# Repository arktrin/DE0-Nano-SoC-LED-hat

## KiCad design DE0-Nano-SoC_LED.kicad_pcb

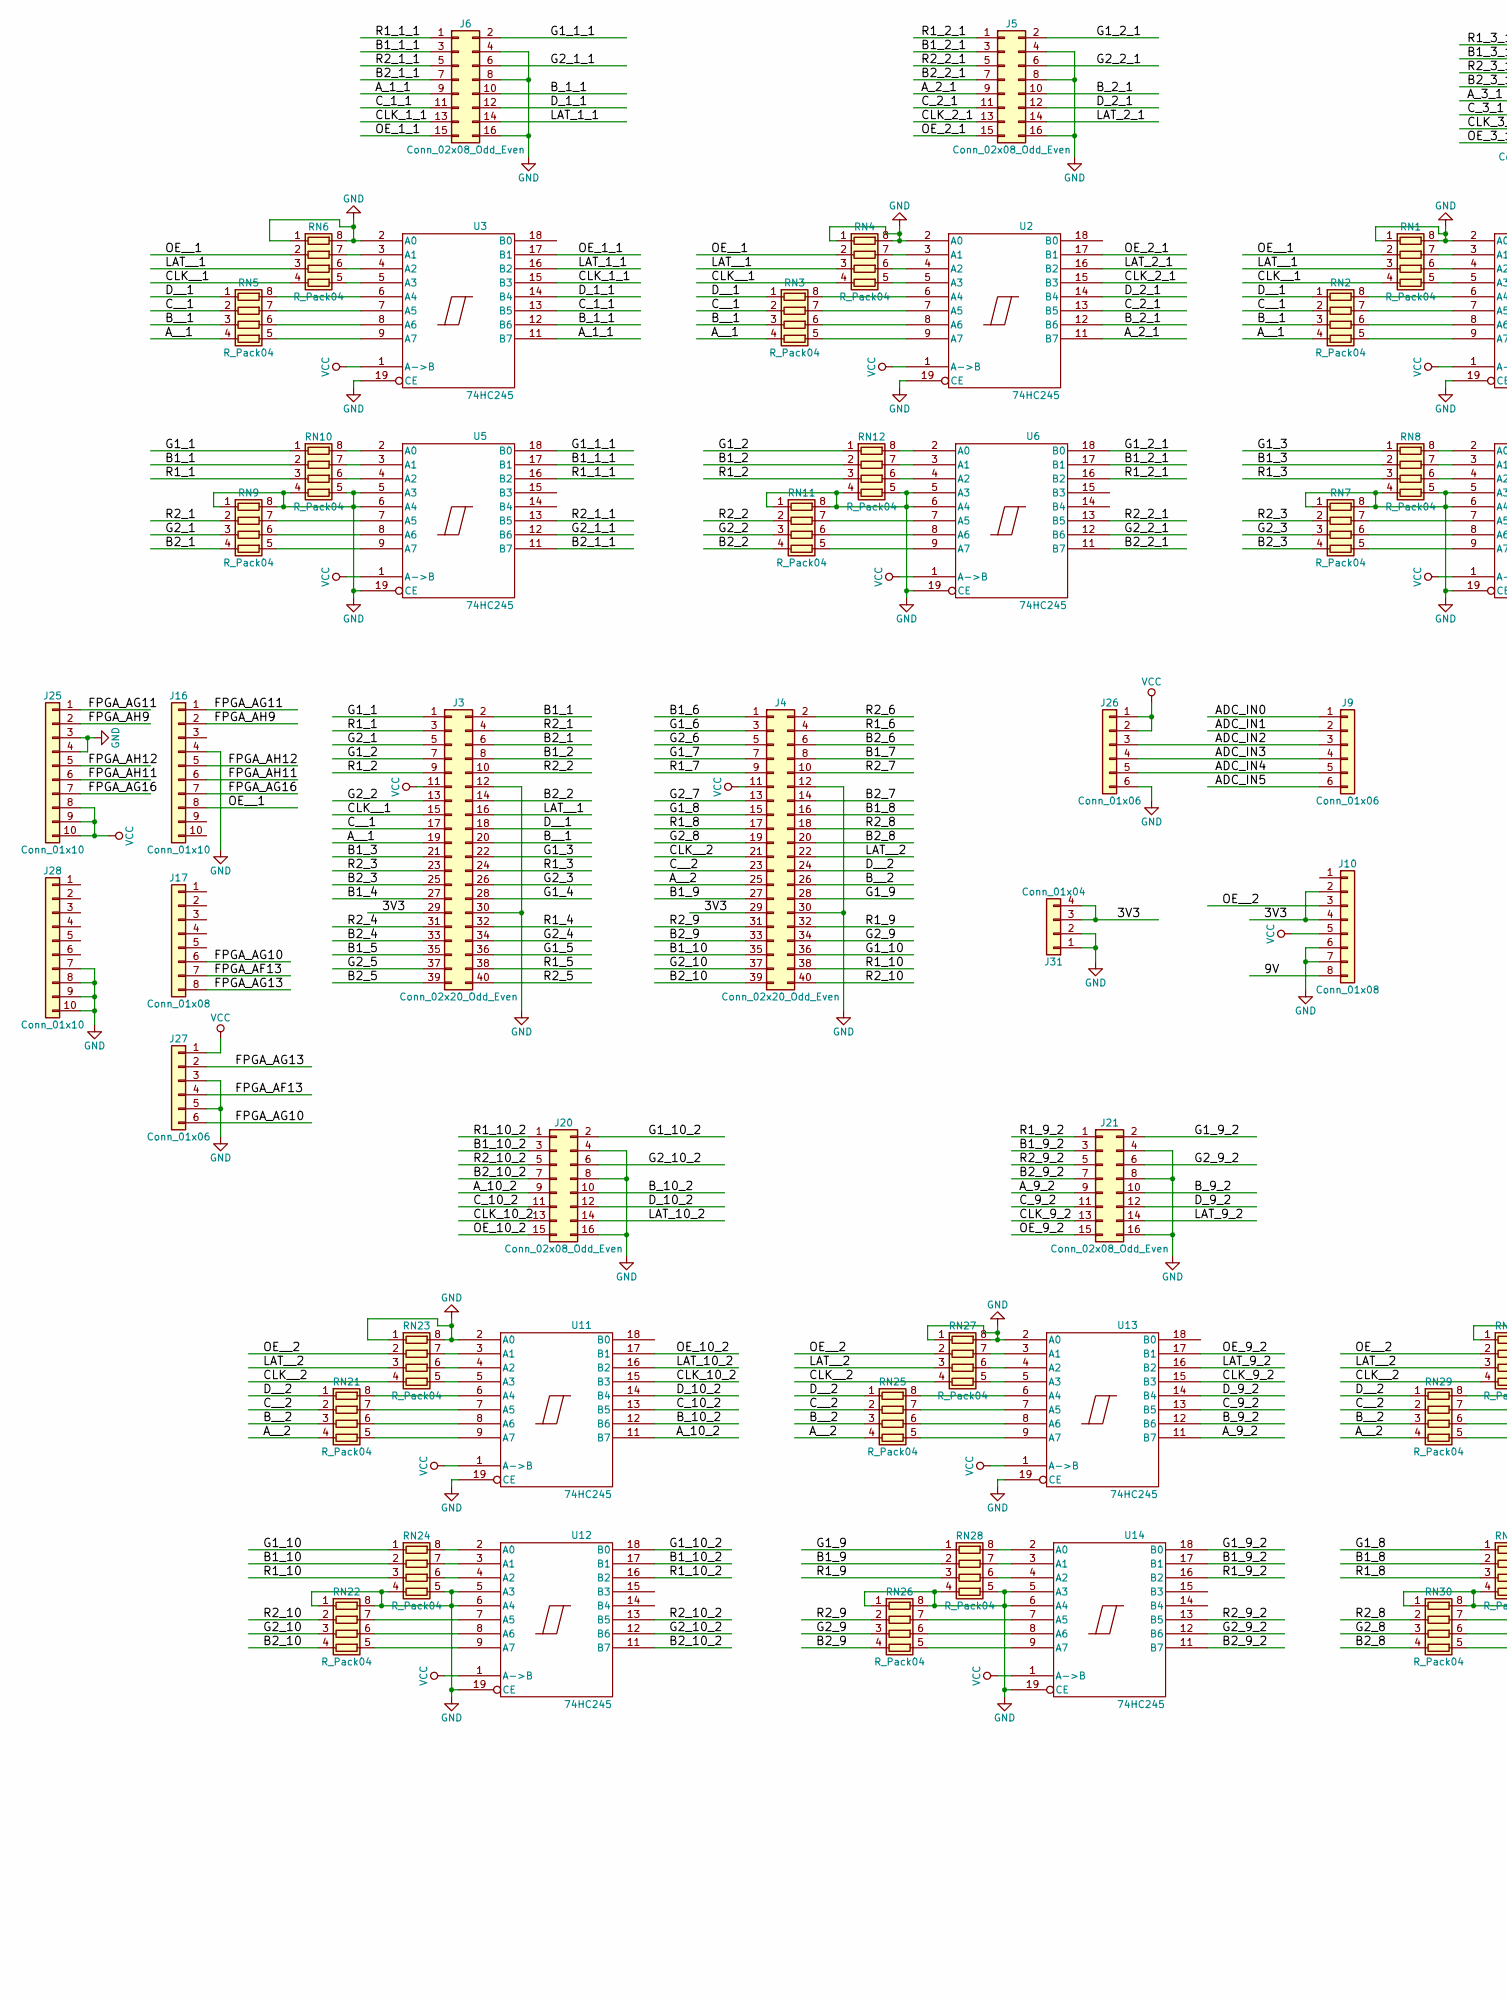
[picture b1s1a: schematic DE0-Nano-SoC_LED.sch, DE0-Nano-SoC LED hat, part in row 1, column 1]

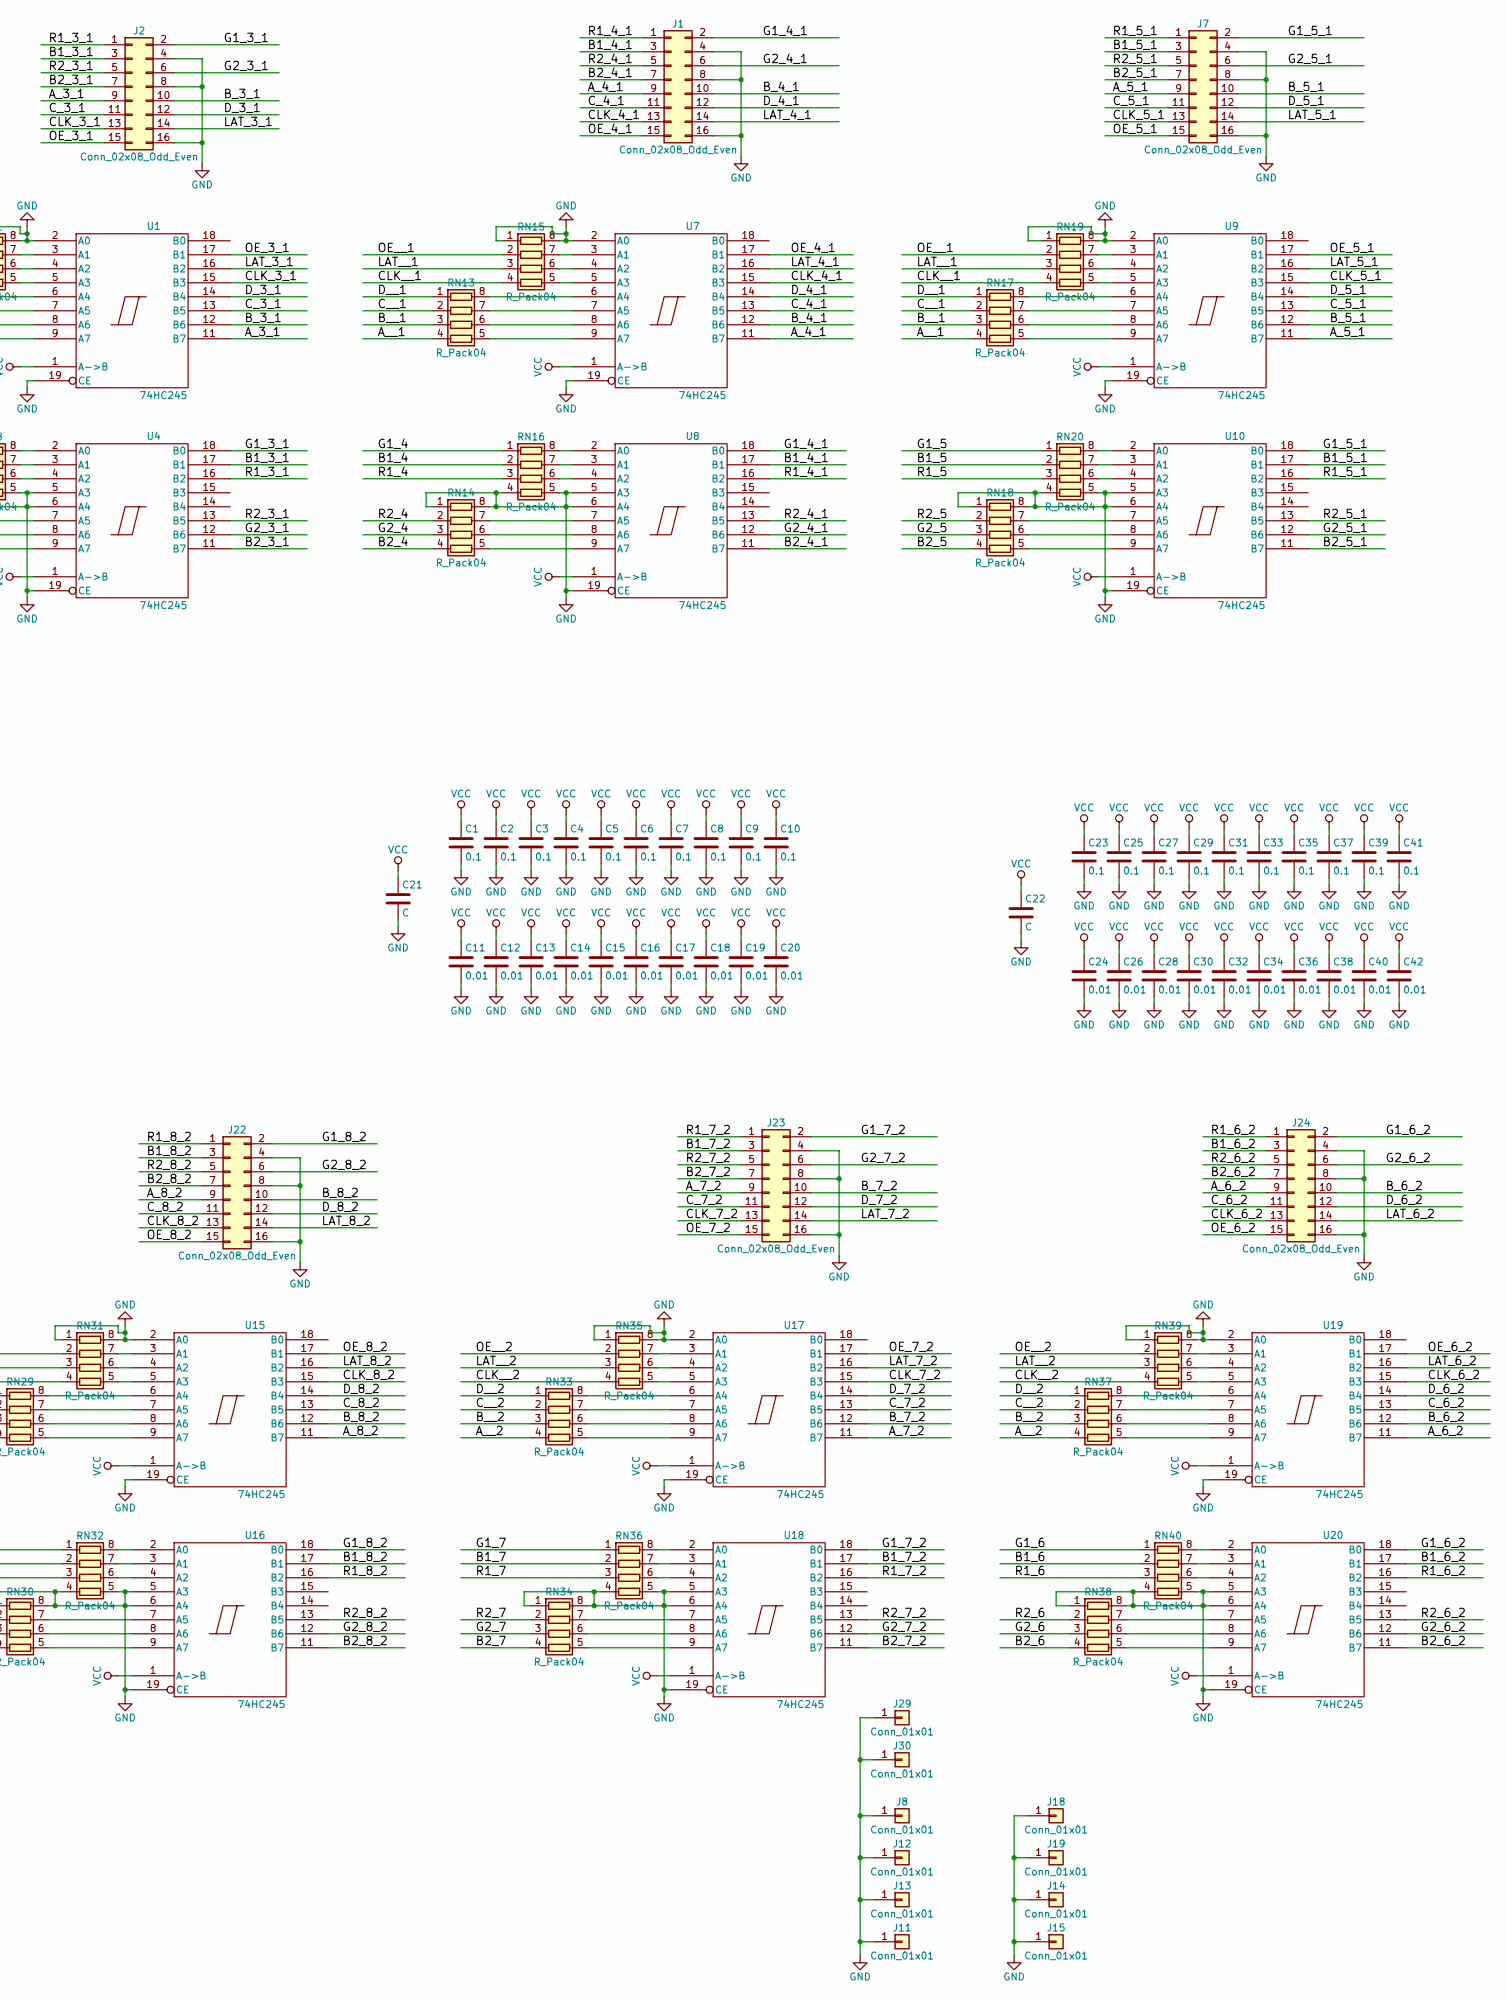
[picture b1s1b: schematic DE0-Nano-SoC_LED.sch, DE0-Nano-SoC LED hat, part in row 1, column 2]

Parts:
C1, C2, C3, C4, C5, C6, C7, C8, C9, C10, C23, C25, C27, C29, C31, C33, C35, C37, C39, C41: 0.1; C_0402_NoSilk
C11, C12, C13, C14, C15, C16, C17, C18, C19, C20, C24, C26, C28, C30, C32, C34, C36, C38, C40, C42: 0.01; C_0402_NoSilk
C21, C22: C; C_1210
J1, J2, J5, J6, J7, J20, J21, J22, J23, J24: Conn_02x08_Odd_Even; Multicomp_MC9A12-1634_2x08x2.54mm_Straight
J3, J4: Conn_02x20_Odd_Even; Pin_Header_Straight_2x20_Pitch2.54mm
J8, J11, J12, J13, J14, J15, J18, J19, J29, J30: Conn_01x01; MountingHole_3.2mm_M3_ISO7380_Pad
J9, J26, J27: Conn_01x06; Pin_Header_Straight_1x06_Pitch2.54mm
J10, J17: Conn_01x08; Pin_Header_Straight_1x08_Pitch2.54mm
J16, J25, J28: Conn_01x10; Pin_Header_Straight_1x10_Pitch2.54mm
J31: Conn_01x04; Pin_Header_Straight_1x04_Pitch2.54mm
RN1, RN2, RN3, RN4, RN5, RN6, RN7, RN8, RN9, RN10, RN11, RN12, RN13, RN14, RN15, RN16, RN17, RN18, RN19, RN20, RN21, RN22, RN23, RN24, RN25, RN26, RN27, RN28, RN29, RN30, RN31, RN32, RN33, RN34, RN35, RN36, RN37, RN38, RN39, RN40: R_Pack04; R_Array_Concave_4x0402
U1, U2, U3, U4, U5, U6, U7, U8, U9, U10, U11, U12, U13, U14, U15, U16, U17, U18, U19, U20: 74HC245; SSOP-20

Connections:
/3V3: J3.29, J4.29, J10.2, J10.4, J31.3, J31.4
/ADC_IN2: J9.3, J26.3
/ADC_IN3: J9.4, J26.4
/ADC_IN4: J9.5, J26.5
/ADC_IN5: J9.6
/A_1_1: J6.9, U3.11 (B7)
/A_2_1: J5.9, U2.11 (B7)
/A_3_1: J2.9, U1.11 (B7)
/A_4_1: J1.9, U7.11 (B7)
/A_5_1: J7.9, U9.11 (B7)
/A_6_2: J24.9, U19.11 (B7)
/A_7_2: J23.9, U17.11 (B7)
/A_8_2: J22.9, U15.11 (B7)
/A_9_2: J21.9, U13.11 (B7)
/A_10_2: J20.9, U11.11 (B7)
/A__1: J3.19, RN2.4 (R4.1), RN3.4 (R4.1), RN5.4 (R4.1), RN13.4 (R4.1), RN17.4 (R4.1)
/A__2: J4.25, RN21.4 (R4.1), RN25.4 (R4.1), RN29.4 (R4.1), RN33.4 (R4.1), RN37.4 (R4.1)
/B1_1: J3.2, RN10.2 (R2.1)
/B1_1_1: J6.3, U5.17 (B1)
/B1_2: J3.8, RN12.2 (R2.1)
/B1_2_1: J5.3, U6.17 (B1)
/B1_3: J3.21, RN8.2 (R2.1)
/B1_3_1: J2.3, U4.17 (B1)
/B1_4: J3.27, RN16.2 (R2.1)
/B1_4_1: J1.3, U8.17 (B1)
/B1_5: J3.35, RN20.2 (R2.1)
/B1_5_1: J7.3, U10.17 (B1)
/B1_6: J4.1, RN40.2 (R2.1)
/B1_6_2: J24.3, U20.17 (B1)
/B1_7: J4.8, RN36.2 (R2.1)
/B1_7_2: J23.3, U18.17 (B1)
/B1_8: J4.16, RN32.2 (R2.1)
/B1_8_2: J22.3, U16.17 (B1)
/B1_9: J4.27, RN28.2 (R2.1)
/B1_9_2: J21.3, U14.17 (B1)
/B1_10: J4.35, RN24.2 (R2.1)
/B1_10_2: J20.3, U12.17 (B1)
/B2_1: J3.6, RN9.4 (R4.1)
/B2_1_1: J6.7, U5.11 (B7)
/B2_2: J3.14, RN11.4 (R4.1)
/B2_2_1: J5.7, U6.11 (B7)
/B2_3: J3.25, RN7.4 (R4.1)
/B2_3_1: J2.7, U4.11 (B7)
/B2_4: J3.33, RN14.4 (R4.1)
/B2_4_1: J1.7, U8.11 (B7)
/B2_5: J3.39, RN18.4 (R4.1)
/B2_5_1: J7.7, U10.11 (B7)
/B2_6: J4.6, RN38.4 (R4.1)
/B2_6_2: J24.7, U20.11 (B7)
/B2_7: J4.14, RN34.4 (R4.1)
/B2_7_2: J23.7, U18.11 (B7)
/B2_8: J4.20, RN30.4 (R4.1)
/B2_8_2: J22.7, U16.11 (B7)
/B2_9: J4.33, RN26.4 (R4.1)
/B2_9_2: J21.7, U14.11 (B7)
/B2_10: J4.39, RN22.4 (R4.1)
/B2_10_2: J20.7, U12.11 (B7)
/B_1_1: J6.10, U3.12 (B6)
/B_2_1: J5.10, U2.12 (B6)
/B_3_1: J2.10, U1.12 (B6)
/B_4_1: J1.10, U7.12 (B6)
/B_5_1: J7.10, U9.12 (B6)
/B_6_2: J24.10, U19.12 (B6)
/B_7_2: J23.10, U17.12 (B6)
/B_8_2: J22.10, U15.12 (B6)
/B_9_2: J21.10, U13.12 (B6)
/B_10_2: J20.10, U11.12 (B6)
/B__1: J3.20, RN2.3 (R3.1), RN3.3 (R3.1), RN5.3 (R3.1), RN13.3 (R3.1), RN17.3 (R3.1)
/B__2: J4.26, RN21.3 (R3.1), RN25.3 (R3.1), RN29.3 (R3.1), RN33.3 (R3.1), RN37.3 (R3.1)
/CLK_1_1: J6.13, U3.15 (B3)
/CLK_2_1: J5.13, U2.15 (B3)
/CLK_3_1: J2.13, U1.15 (B3)
/CLK_4_1: J1.13, U7.15 (B3)
/CLK_5_1: J7.13, U9.15 (B3)
/CLK_6_2: J24.13, U19.15 (B3)
/CLK_7_2: J23.13, U17.15 (B3)
/CLK_8_2: J22.13, U15.15 (B3)
/CLK_9_2: J21.13, U13.15 (B3)
/CLK_10_2: J20.13, U11.15 (B3)
/CLK__1: J3.15, RN1.4 (R4.1), RN4.4 (R4.1), RN6.4 (R4.1), RN15.4 (R4.1), RN19.4 (R4.1)
/CLK__2: J4.21, RN23.4 (R4.1), RN27.4 (R4.1), RN31.4 (R4.1), RN35.4 (R4.1), RN39.4 (R4.1)
/C_1_1: J6.11, U3.13 (B5)
/C_2_1: J5.11, U2.13 (B5)
/C_3_1: J2.11, U1.13 (B5)
/C_4_1: J1.11, U7.13 (B5)
/C_5_1: J7.11, U9.13 (B5)
/C_6_2: J24.11, U19.13 (B5)
/C_7_2: J23.11, U17.13 (B5)
/C_8_2: J22.11, U15.13 (B5)
/C_9_2: J21.11, U13.13 (B5)
/C_10_2: J20.11, U11.13 (B5)
/C__1: J3.17, RN2.2 (R2.1), RN3.2 (R2.1), RN5.2 (R2.1), RN13.2 (R2.1), RN17.2 (R2.1)
/C__2: J4.23, RN21.2 (R2.1), RN25.2 (R2.1), RN29.2 (R2.1), RN33.2 (R2.1), RN37.2 (R2.1)
/D_1_1: J6.12, U3.14 (B4)
/D_2_1: J5.12, U2.14 (B4)
/D_3_1: J2.12, U1.14 (B4)
/D_4_1: J1.12, U7.14 (B4)
/D_5_1: J7.12, U9.14 (B4)
/D_6_2: J24.12, U19.14 (B4)
/D_7_2: J23.12, U17.14 (B4)
/D_8_2: J22.12, U15.14 (B4)
/D_9_2: J21.12, U13.14 (B4)
/D_10_2: J20.12, U11.14 (B4)
/D__1: J3.18, RN2.1 (R1.1), RN3.1 (R1.1), RN5.1 (R1.1), RN13.1 (R1.1), RN17.1 (R1.1)
/D__2: J4.24, RN21.1 (R1.1), RN25.1 (R1.1), RN29.1 (R1.1), RN33.1 (R1.1), RN37.1 (R1.1)
/FPGA_AF13: J17.7, J27.4
/FPGA_AG10: J17.6, J27.6
/FPGA_AG11: J16.1, J25.1
/FPGA_AG13: J17.8, J27.2
/FPGA_AG16: J16.7, J25.7
/FPGA_AH9: J16.2, J25.2
/FPGA_AH11: J16.6, J25.6
/FPGA_AH12: J16.5, J25.5
/G1_1: J3.1, RN10.1 (R1.1)
/G1_1_1: J6.2, U5.18 (B0)
/G1_2: J3.7, RN12.1 (R1.1)
/G1_2_1: J5.2, U6.18 (B0)
/G1_3: J3.22, RN8.1 (R1.1)
/G1_3_1: J2.2, U4.18 (B0)
/G1_4: J3.28, RN16.1 (R1.1)
/G1_4_1: J1.2, U8.18 (B0)
/G1_5: J3.36, RN20.1 (R1.1)
/G1_5_1: J7.2, U10.18 (B0)
/G1_6: J4.3, RN40.1 (R1.1)
/G1_6_2: J24.2, U20.18 (B0)
/G1_7: J4.7, RN36.1 (R1.1)
/G1_7_2: J23.2, U18.18 (B0)
/G1_8: J4.15, RN32.1 (R1.1)
/G1_8_2: J22.2, U16.18 (B0)
/G1_9: J4.28, RN28.1 (R1.1)
/G1_9_2: J21.2, U14.18 (B0)
/G1_10: J4.36, RN24.1 (R1.1)
/G1_10_2: J20.2, U12.18 (B0)
/G2_1: J3.5, RN9.3 (R3.1)
/G2_1_1: J6.6, U5.12 (B6)
/G2_2: J3.13, RN11.3 (R3.1)
/G2_2_1: J5.6, U6.12 (B6)
/G2_3: J3.26, RN7.3 (R3.1)
/G2_3_1: J2.6, U4.12 (B6)
/G2_4: J3.34, RN14.3 (R3.1)
/G2_4_1: J1.6, U8.12 (B6)
/G2_5: J3.37, RN18.3 (R3.1)
/G2_5_1: J7.6, U10.12 (B6)
/G2_6: J4.5, RN38.3 (R3.1)
/G2_6_2: J24.6, U20.12 (B6)
/G2_7: J4.13, RN34.3 (R3.1)
/G2_7_2: J23.6, U18.12 (B6)
/G2_8: J4.19, RN30.3 (R3.1)
/G2_8_2: J22.6, U16.12 (B6)
/G2_9: J4.34, RN26.3 (R3.1)
/G2_9_2: J21.6, U14.12 (B6)
/G2_10: J4.37, RN22.3 (R3.1)
/G2_10_2: J20.6, U12.12 (B6)
/LAT_1_1: J6.14, U3.16 (B2)
/LAT_2_1: J5.14, U2.16 (B2)
/LAT_3_1: J2.14, U1.16 (B2)
/LAT_4_1: J1.14, U7.16 (B2)
/LAT_5_1: J7.14, U9.16 (B2)
/LAT_6_2: J24.14, U19.16 (B2)
/LAT_7_2: J23.14, U17.16 (B2)
/LAT_8_2: J22.14, U15.16 (B2)
/LAT_9_2: J21.14, U13.16 (B2)
/LAT_10_2: J20.14, U11.16 (B2)
/LAT__1: J3.16, RN1.3 (R3.1), RN4.3 (R3.1), RN6.3 (R3.1), RN15.3 (R3.1), RN19.3 (R3.1)
/LAT__2: J4.22, RN23.3 (R3.1), RN27.3 (R3.1), RN31.3 (R3.1), RN35.3 (R3.1), RN39.3 (R3.1)
/OE_1_1: J6.15, U3.17 (B1)
/OE_2_1: J5.15, U2.17 (B1)
/OE_3_1: J2.15, U1.17 (B1)
/OE_4_1: J1.15, U7.17 (B1)
/OE_5_1: J7.15, U9.17 (B1)
/OE_6_2: J24.15, U19.17 (B1)
/OE_7_2: J23.15, U17.17 (B1)
/OE_8_2: J22.15, U15.17 (B1)
/OE_9_2: J21.15, U13.17 (B1)
/OE_10_2: J20.15, U11.17 (B1)
/OE__1: J16.8, RN1.2 (R2.1), RN4.2 (R2.1), RN6.2 (R2.1), RN15.2 (R2.1), RN19.2 (R2.1)
/OE__2: J10.3, RN23.2 (R2.1), RN27.2 (R2.1), RN31.2 (R2.1), RN35.2 (R2.1), RN39.2 (R2.1)
/R1_1: J3.3, RN10.3 (R3.1)
/R1_1_1: J6.1, U5.16 (B2)
/R1_2: J3.9, RN12.3 (R3.1)
/R1_2_1: J5.1, U6.16 (B2)
/R1_3: J3.24, RN8.3 (R3.1)
/R1_3_1: J2.1, U4.16 (B2)
/R1_4: J3.32, RN16.3 (R3.1)
/R1_4_1: J1.1, U8.16 (B2)
/R1_5: J3.38, RN20.3 (R3.1)
/R1_5_1: J7.1, U10.16 (B2)
/R1_6: J4.4, RN40.3 (R3.1)
/R1_6_2: J24.1, U20.16 (B2)
/R1_7: J4.9, RN36.3 (R3.1)
/R1_7_2: J23.1, U18.16 (B2)
/R1_8: J4.17, RN32.3 (R3.1)
/R1_8_2: J22.1, U16.16 (B2)
/R1_9: J4.32, RN28.3 (R3.1)
/R1_9_2: J21.1, U14.16 (B2)
/R1_10: J4.38, RN24.3 (R3.1)
/R1_10_2: J20.1, U12.16 (B2)
/R2_1: J3.4, RN9.2 (R2.1)
/R2_1_1: J6.5, U5.13 (B5)
/R2_2: J3.10, RN11.2 (R2.1)
/R2_2_1: J5.5, U6.13 (B5)
/R2_3: J3.23, RN7.2 (R2.1)
/R2_3_1: J2.5, U4.13 (B5)
/R2_4: J3.31, RN14.2 (R2.1)
/R2_4_1: J1.5, U8.13 (B5)
/R2_5: J3.40, RN18.2 (R2.1)
/R2_5_1: J7.5, U10.13 (B5)
/R2_6: J4.2, RN38.2 (R2.1)
/R2_6_2: J24.5, U20.13 (B5)
/R2_7: J4.10, RN34.2 (R2.1)
/R2_7_2: J23.5, U18.13 (B5)
/R2_8: J4.18, RN30.2 (R2.1)
/R2_8_2: J22.5, U16.13 (B5)
/R2_9: J4.31, RN26.2 (R2.1)
/R2_9_2: J21.5, U14.13 (B5)
/R2_10: J4.40, RN22.2 (R2.1)
/R2_10_2: J20.5, U12.13 (B5)
GND: C1.2, C2.2, C3.2, C4.2, C5.2, C6.2, C7.2, C8.2, C9.2, C10.2, C11.2, C12.2, C13.2, C14.2, C15.2, C16.2, C17.2, C18.2, C19.2, C20.2, C21.2, C22.2, C23.2, C24.2, C25.2, C26.2, C27.2, C28.2, C29.2, C30.2, C31.2, C32.2, C33.2, C34.2, C35.2, C36.2, C37.2, C38.2, C39.2, C40.2, C41.2, C42.2, J1.4, J1.8, J1.16, J2.4, J2.8, J2.16, J3.12, J3.30, J4.12, J4.30, J5.4, J5.8, J5.16, J6.4, J6.8, J6.16, J7.4, J7.8, J7.16, J8.1, J10.6, J10.7, J11.1, J12.1, J13.1, J14.1, J15.1, J16.4, J18.1, J19.1, J20.4, J20.8, J20.16, J21.4, J21.8, J21.16, J22.4, J22.8, J22.16, J23.4, J23.8, J23.16, J24.4, J24.8, J24.16, J25.3, J25.4, J26.6, J27.3, J27.5, J28.7, J28.8, J28.9, J28.10, J29.1, J30.1, J31.1, J31.2, RN1.1 (R1.1), RN1.8 (R1.2), RN4.1 (R1.1), RN4.8 (R1.2), RN6.1 (R1.1), RN6.8 (R1.2), RN7.1 (R1.1), RN7.8 (R1.2), RN8.4 (R4.1), RN8.5 (R4.2), RN9.1 (R1.1), RN9.8 (R1.2), RN10.4 (R4.1), RN10.5 (R4.2), RN11.1 (R1.1), RN11.8 (R1.2), RN12.4 (R4.1), RN12.5 (R4.2), RN14.1 (R1.1), RN14.8 (R1.2), RN15.1 (R1.1), RN15.8 (R1.2), RN16.4 (R4.1), RN16.5 (R4.2), RN18.1 (R1.1), RN18.8 (R1.2), RN19.1 (R1.1), RN19.8 (R1.2), RN20.4 (R4.1), RN20.5 (R4.2), RN22.1 (R1.1), RN22.8 (R1.2), RN23.1 (R1.1), RN23.8 (R1.2), RN24.4 (R4.1), RN24.5 (R4.2), RN26.1 (R1.1), RN26.8 (R1.2), RN27.1 (R1.1), RN27.8 (R1.2), RN28.4 (R4.1), RN28.5 (R4.2), RN30.1 (R1.1), RN30.8 (R1.2), RN31.1 (R1.1), RN31.8 (R1.2), RN32.4 (R4.1), RN32.5 (R4.2), RN34.1 (R1.1), RN34.8 (R1.2), RN35.1 (R1.1), RN35.8 (R1.2), RN36.4 (R4.1), RN36.5 (R4.2), RN38.1 (R1.1), RN38.8 (R1.2), RN39.1 (R1.1), RN39.8 (R1.2), RN40.4 (R4.1), RN40.5 (R4.2), U1.2 (A0), U1.10 (GND), U1.19 (CE), U2.2 (A0), U2.10 (GND), U2.19 (CE), U3.2 (A0), U3.10 (GND), U3.19 (CE), U4.5 (A3), U4.6 (A4), U4.10 (GND), U4.19 (CE), U5.5 (A3), U5.6 (A4), U5.10 (GND), U5.19 (CE), U6.5 (A3), U6.6 (A4), U6.10 (GND), U6.19 (CE), U7.2 (A0), U7.10 (GND), U7.19 (CE), U8.5 (A3), U8.6 (A4), U8.10 (GND), U8.19 (CE), U9.2 (A0), U9.10 (GND), U9.19 (CE), U10.5 (A3), U10.6 (A4), U10.10 (GND), U10.19 (CE), U11.2 (A0), U11.10 (GND), U11.19 (CE), U12.5 (A3), U12.6 (A4), U12.10 (GND), U12.19 (CE), U13.2 (A0), U13.10 (GND), U13.19 (CE), U14.5 (A3), U14.6 (A4), U14.10 (GND), U14.19 (CE), U15.2 (A0), U15.10 (GND), U15.19 (CE), U16.5 (A3), U16.6 (A4), U16.10 (GND), U16.19 (CE), U17.2 (A0), U17.10 (GND), U17.19 (CE), U18.5 (A3), U18.6 (A4), U18.10 (GND), U18.19 (CE), U19.2 (A0), U19.10 (GND), U19.19 (CE), U20.5 (A3), U20.6 (A4), U20.10 (GND), U20.19 (CE)
unnamed: RN1.5 (R4.2), U1.5 (A3)
unnamed: RN1.6 (R3.2), U1.4 (A2)
unnamed: RN1.7 (R2.2), U1.3 (A1)
unnamed: RN2.5 (R4.2), U1.9 (A7)
unnamed: RN2.6 (R3.2), U1.8 (A6)
unnamed: RN2.7 (R2.2), U1.7 (A5)
unnamed: RN2.8 (R1.2), U1.6 (A4)
unnamed: RN3.5 (R4.2), U2.9 (A7)
unnamed: RN3.6 (R3.2), U2.8 (A6)
unnamed: RN3.7 (R2.2), U2.7 (A5)
unnamed: RN3.8 (R1.2), U2.6 (A4)
unnamed: RN4.5 (R4.2), U2.5 (A3)
unnamed: RN4.6 (R3.2), U2.4 (A2)
unnamed: RN4.7 (R2.2), U2.3 (A1)
unnamed: RN5.5 (R4.2), U3.9 (A7)
unnamed: RN5.6 (R3.2), U3.8 (A6)
unnamed: RN5.7 (R2.2), U3.7 (A5)
unnamed: RN5.8 (R1.2), U3.6 (A4)
unnamed: RN6.5 (R4.2), U3.5 (A3)
unnamed: RN6.6 (R3.2), U3.4 (A2)
unnamed: RN6.7 (R2.2), U3.3 (A1)
unnamed: RN7.5 (R4.2), U4.9 (A7)
unnamed: RN7.6 (R3.2), U4.8 (A6)
unnamed: RN7.7 (R2.2), U4.7 (A5)
unnamed: RN8.6 (R3.2), U4.4 (A2)
unnamed: RN8.7 (R2.2), U4.3 (A1)
unnamed: RN8.8 (R1.2), U4.2 (A0)
unnamed: RN9.5 (R4.2), U5.9 (A7)
unnamed: RN9.6 (R3.2), U5.8 (A6)
unnamed: RN9.7 (R2.2), U5.7 (A5)
unnamed: RN10.6 (R3.2), U5.4 (A2)
unnamed: RN10.7 (R2.2), U5.3 (A1)
unnamed: RN10.8 (R1.2), U5.2 (A0)
unnamed: RN11.5 (R4.2), U6.9 (A7)
unnamed: RN11.6 (R3.2), U6.8 (A6)
unnamed: RN11.7 (R2.2), U6.7 (A5)
unnamed: RN12.6 (R3.2), U6.4 (A2)
unnamed: RN12.7 (R2.2), U6.3 (A1)
unnamed: RN12.8 (R1.2), U6.2 (A0)
unnamed: RN13.5 (R4.2), U7.9 (A7)
unnamed: RN13.6 (R3.2), U7.8 (A6)
unnamed: RN13.7 (R2.2), U7.7 (A5)
unnamed: RN13.8 (R1.2), U7.6 (A4)
unnamed: RN14.5 (R4.2), U8.9 (A7)
unnamed: RN14.6 (R3.2), U8.8 (A6)
unnamed: RN14.7 (R2.2), U8.7 (A5)
unnamed: RN15.5 (R4.2), U7.5 (A3)
unnamed: RN15.6 (R3.2), U7.4 (A2)
unnamed: RN15.7 (R2.2), U7.3 (A1)
unnamed: RN16.6 (R3.2), U8.4 (A2)
unnamed: RN16.7 (R2.2), U8.3 (A1)
unnamed: RN16.8 (R1.2), U8.2 (A0)
unnamed: RN17.5 (R4.2), U9.9 (A7)
unnamed: RN17.6 (R3.2), U9.8 (A6)
unnamed: RN17.7 (R2.2), U9.7 (A5)
unnamed: RN17.8 (R1.2), U9.6 (A4)
unnamed: RN18.5 (R4.2), U10.9 (A7)
unnamed: RN18.6 (R3.2), U10.8 (A6)
unnamed: RN18.7 (R2.2), U10.7 (A5)
unnamed: RN19.5 (R4.2), U9.5 (A3)
unnamed: RN19.6 (R3.2), U9.4 (A2)
unnamed: RN19.7 (R2.2), U9.3 (A1)
unnamed: RN20.6 (R3.2), U10.4 (A2)
unnamed: RN20.7 (R2.2), U10.3 (A1)
unnamed: RN20.8 (R1.2), U10.2 (A0)
unnamed: RN21.5 (R4.2), U11.9 (A7)
unnamed: RN21.6 (R3.2), U11.8 (A6)
unnamed: RN21.7 (R2.2), U11.7 (A5)
unnamed: RN21.8 (R1.2), U11.6 (A4)
unnamed: RN22.5 (R4.2), U12.9 (A7)
unnamed: RN22.6 (R3.2), U12.8 (A6)
unnamed: RN22.7 (R2.2), U12.7 (A5)
unnamed: RN23.5 (R4.2), U11.5 (A3)
unnamed: RN23.6 (R3.2), U11.4 (A2)
unnamed: RN23.7 (R2.2), U11.3 (A1)
unnamed: RN24.6 (R3.2), U12.4 (A2)
unnamed: RN24.7 (R2.2), U12.3 (A1)
unnamed: RN24.8 (R1.2), U12.2 (A0)
unnamed: RN25.5 (R4.2), U13.9 (A7)
unnamed: RN25.6 (R3.2), U13.8 (A6)
unnamed: RN25.7 (R2.2), U13.7 (A5)
unnamed: RN25.8 (R1.2), U13.6 (A4)
unnamed: RN26.5 (R4.2), U14.9 (A7)
unnamed: RN26.6 (R3.2), U14.8 (A6)
unnamed: RN26.7 (R2.2), U14.7 (A5)
unnamed: RN27.5 (R4.2), U13.5 (A3)
unnamed: RN27.6 (R3.2), U13.4 (A2)
unnamed: RN27.7 (R2.2), U13.3 (A1)
unnamed: RN28.6 (R3.2), U14.4 (A2)
unnamed: RN28.7 (R2.2), U14.3 (A1)
unnamed: RN28.8 (R1.2), U14.2 (A0)
unnamed: RN29.5 (R4.2), U15.9 (A7)
unnamed: RN29.6 (R3.2), U15.8 (A6)
unnamed: RN29.7 (R2.2), U15.7 (A5)
unnamed: RN29.8 (R1.2), U15.6 (A4)
unnamed: RN30.5 (R4.2), U16.9 (A7)
unnamed: RN30.6 (R3.2), U16.8 (A6)
unnamed: RN30.7 (R2.2), U16.7 (A5)
unnamed: RN31.5 (R4.2), U15.5 (A3)
unnamed: RN31.6 (R3.2), U15.4 (A2)
unnamed: RN31.7 (R2.2), U15.3 (A1)
unnamed: RN32.6 (R3.2), U16.4 (A2)
unnamed: RN32.7 (R2.2), U16.3 (A1)
unnamed: RN32.8 (R1.2), U16.2 (A0)
unnamed: RN33.5 (R4.2), U17.9 (A7)
unnamed: RN33.6 (R3.2), U17.8 (A6)
unnamed: RN33.7 (R2.2), U17.7 (A5)
unnamed: RN33.8 (R1.2), U17.6 (A4)
unnamed: RN34.5 (R4.2), U18.9 (A7)
unnamed: RN34.6 (R3.2), U18.8 (A6)
unnamed: RN34.7 (R2.2), U18.7 (A5)
unnamed: RN35.5 (R4.2), U17.5 (A3)
unnamed: RN35.6 (R3.2), U17.4 (A2)
unnamed: RN35.7 (R2.2), U17.3 (A1)
unnamed: RN36.6 (R3.2), U18.4 (A2)
unnamed: RN36.7 (R2.2), U18.3 (A1)
unnamed: RN36.8 (R1.2), U18.2 (A0)
unnamed: RN37.5 (R4.2), U19.9 (A7)
unnamed: RN37.6 (R3.2), U19.8 (A6)
unnamed: RN37.7 (R2.2), U19.7 (A5)
unnamed: RN37.8 (R1.2), U19.6 (A4)
unnamed: RN38.5 (R4.2), U20.9 (A7)
unnamed: RN38.6 (R3.2), U20.8 (A6)
unnamed: RN38.7 (R2.2), U20.7 (A5)
unnamed: RN39.5 (R4.2), U19.5 (A3)
unnamed: RN39.6 (R3.2), U19.4 (A2)
unnamed: RN39.7 (R2.2), U19.3 (A1)
unnamed: RN40.6 (R3.2), U20.4 (A2)
unnamed: RN40.7 (R2.2), U20.3 (A1)
unnamed: RN40.8 (R1.2), U20.2 (A0)
VCC: C1.1, C2.1, C3.1, C4.1, C5.1, C6.1, C7.1, C8.1, C9.1, C10.1, C11.1, C12.1, C13.1, C14.1, C15.1, C16.1, C17.1, C18.1, C19.1, C20.1, C21.1, C22.1, C23.1, C24.1, C25.1, C26.1, C27.1, C28.1, C29.1, C30.1, C31.1, C32.1, C33.1, C34.1, C35.1, C36.1, C37.1, C38.1, C39.1, C40.1, C41.1, C42.1, J3.11, J4.11, J10.5, J25.8, J25.9, J25.10, J26.1, J26.2, J27.1, U1.1 (A->B), U1.20 (VCC), U2.1 (A->B), U2.20 (VCC), U3.1 (A->B), U3.20 (VCC), U4.1 (A->B), U4.20 (VCC), U5.1 (A->B), U5.20 (VCC), U6.1 (A->B), U6.20 (VCC), U7.1 (A->B), U7.20 (VCC), U8.1 (A->B), U8.20 (VCC), U9.1 (A->B), U9.20 (VCC), U10.1 (A->B), U10.20 (VCC), U11.1 (A->B), U11.20 (VCC), U12.1 (A->B), U12.20 (VCC), U13.1 (A->B), U13.20 (VCC), U14.1 (A->B), U14.20 (VCC), U15.1 (A->B), U15.20 (VCC), U16.1 (A->B), U16.20 (VCC), U17.1 (A->B), U17.20 (VCC), U18.1 (A->B), U18.20 (VCC), U19.1 (A->B), U19.20 (VCC), U20.1 (A->B), U20.20 (VCC)

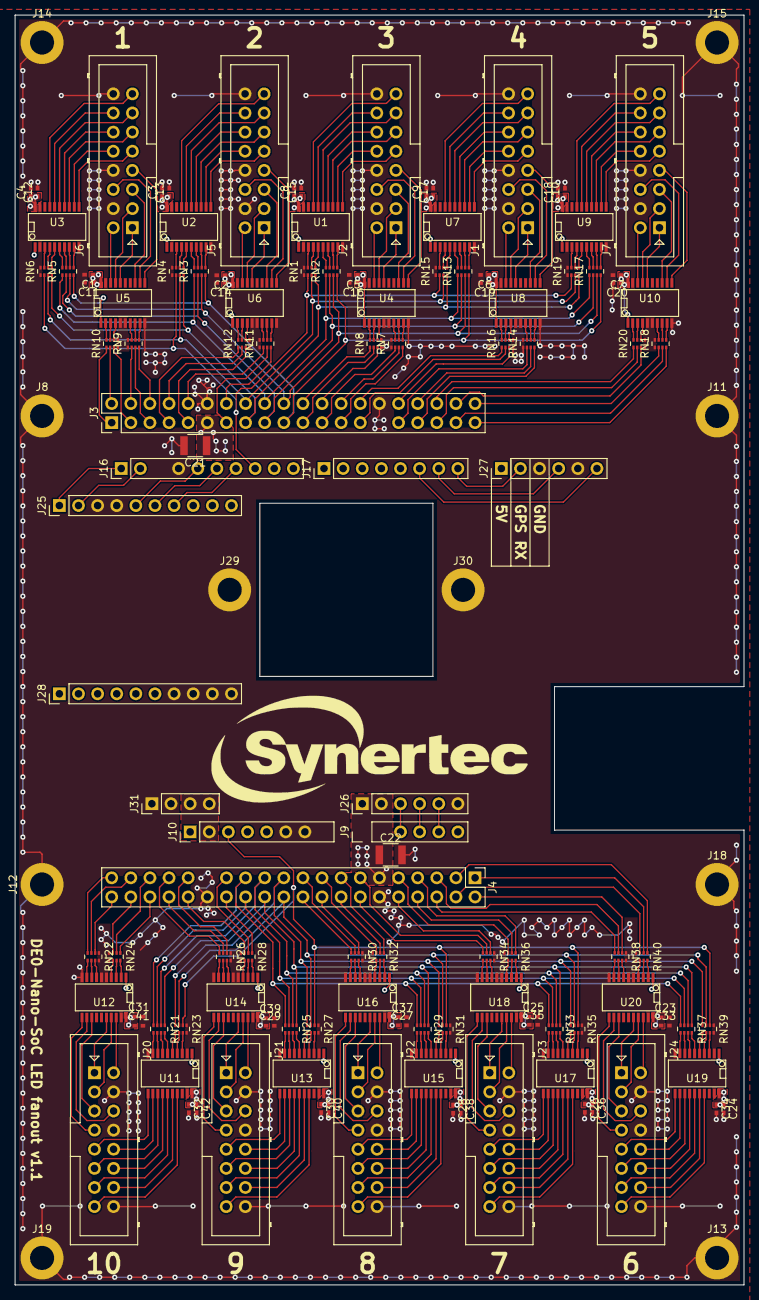
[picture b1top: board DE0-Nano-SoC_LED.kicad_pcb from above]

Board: 2 copper layers, 96.8 x 168.7 mm, 134 parts (0 on the bottom side), 348 nets.

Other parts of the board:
G10: LOGO

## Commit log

2017-12-05 main DE0-Nano-SoC connectors are finally locked in their places
2017-12-05 still in connectors placement phase
2017-12-05 add more connectors
2017-12-06 half of the components are almost placed
2017-12-06 a lot of progress on pcb
2017-12-06 more progress on pcb
2017-12-07 pcb is almost done
2017-12-07 remove unused pins on pcb only
2017-12-07 generate gerber
2017-12-07 small fix on pcb
2017-12-07 small improvemets in pcb
2017-12-08 supa small fix
2017-12-10 remove mask in hope of better GND
2017-12-10 remove custom unused library
2017-12-10 regenerate gerber files
2017-12-10 small pcb improvements and fixes
2017-12-10 regenerate gerber files again
2017-12-10 mask cleanup
2017-12-10 final version of half board
2017-12-14 add pin table
2018-01-17 back to full board
2018-01-17 no change in pcb
2018-01-17 pin rename
2018-01-17 almost all components
2018-01-17 small pcb fix
2018-01-18 components placement continue
2018-01-18 parts autoalign works! (not worth it)
2018-01-18 parts auto align was a stupid idea
2018-01-18 pin swapping
2018-01-19 some progress on pcb
2018-01-20 2 unconnected nets remain
2018-01-21 vias, keepouts, etc ...
2018-01-22 pcb almost done
2018-01-23 small change in pcb
2018-01-24 silk and logo added, gerber generated
2018-01-24 new connectors
2018-01-25 what should I add to the board?
2018-01-25 final version of the board
2018-01-30 pin table update
2018-02-02 pin table fix
2018-02-04 supa small pcb fix
2018-02-07 silk small fix
2018-02-09 final 1.1 version
